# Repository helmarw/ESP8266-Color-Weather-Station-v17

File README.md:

#  Enhanced ESP8266 Color Weather Station w/ Touchscreen -- (Version v17, Open Weather Map) (based on original by Daniel Eichorn (squix78) modified for DHT22)

Original desctiption and instructions see here: https://github.com/fowlerk/ESP8266-Color-Weather-Station-v17

Changes:
 mod for DHTesp.h and DHT22, if you want to use DHT11 you have to change the line 
 dht.setup(DHTPIN, DHTesp::DHT22); and replace DHT22 by DHT11
 had to change some wiring, LED=D0, CS=D8 and DHT=D1, details see below
 added WiFiManager.h v01.14 zu src, since its the last one which is working with this code

## Wiring

| ILI9341   | NodeMCU | WeMos D1 Mini |  Comments | 
| --------- |:---------:|:---------------:|:---------------:|
| T_IRQ     | D4    | D4  |  |
| T_DO      | D6    | D6  |  |
| T_DIN     | D7    | D7  |  |
| T_CS      | D3    | D3  |  |
| T_CLK     | D5    | D5  |  |
| SDO/MISO  | D6    | D6  |  |
| LED       | D0    | D0  | since LED doesnt need interrupt, default was D8 |
| SCK       | D5    | D5  |  |
| SDI/MOSI  | D7    | D7  |  |
| DC/RS     | D2    | D2  |  |
| RESET     | RST   | RST |  |
| CS        | D8    | D8  | needed D1 for DHT, since DHT and D8 crashed ESP, default was D1 |
| GND       | GND   | GND |  |
| VCC       | 3V3   | 3V3 |  |
| DHTdata   | D1    | D1  |  |
| DHTV+     | 3V3   | 3V3 |  |
| DHTGND    | GND   | GND |  |

**Note that I have not tested the NodeMCU 

##  Contributed Libraries / Core / IDE (and links)

Library / Core Referenced | Version | Description | Link
------------------ | ------- | ----------- | ----
**Arduino IDE** | 1.8.10 | Arduino IDE | <https://www.arduino.cc/en/Main/Software>
**ESP8266 core** | 2.5.2 | ESP8266 board definitions | <https://arduino-esp8266.readthedocs.io/en/2.5.2/installing.html>
**<FS.h>** | 2.5.2 | Part of ESP8266 core, SPIFFS filesystem support | <https://arduino-esp8266.readthedocs.io/en/2.5.2/installing.html>
**<Adafruit_GFX.h>** | 1.3.4 | Adafruit's core graphics library | <https://github.com/adafruit/Adafruit-GFX-Library>
**<Adafruit_ILI9341.h>** | 1.2.0 | Adafruit's ILI9341 LCD hardware-specific library | <https://github.com/adafruit/Adafruit_ILI9341>
**<SPI.h>** | 2.5.2 | Part of ESP8266 core, used for DHT temperature readings if used | <https://arduino-esp8266.readthedocs.io/en/2.5.2/installing.html>
**<math.h>** | 1.6.23 | Part of Arduino core, advanced math functions used for calculating wind-chill/heat-index
**<XPT2046_Touchscreen.h>** | 1.2.0 | XPT2046 library for touch-screen controller by Paul Stoffregen | <https://github.com/PaulStoffregen/XPT2046_Touchscreen>
**<WiFiManager.h>** | 0.14.0 | WiFi Manager library by Tzapu | <https://github.com/tzapu/WiFiManager> added to source
**<ArduinoJson.h>** | 5.13.4 | JSON library by Bblanchon | <https://github.com/bblanchon/ArduinoJson>
**<JsonListener.h>** | 1.0.5 | JSON streaming parser by Squix78 | <https://github.com/squix78/json-streaming-parser>
**<OpenWeatherMapCurrent.h>** | 1.6.6 | ESP8266 Weather Station client library by Squix78 - current conditions | <https://github.com/squix78/esp8266-weather-station>
**<OpenWeatherMapForecast.h>** | 1.6.6 | ESP8266 Weather Station client library by Squix78 - 5-day forecast | <https://github.com/squix78/esp8266-weather-station>
**<Astronomy.h>** | 1.6.6 | ESP8266 Weather Station Astronomy client library by Squix78 - sunrise/set, moon illumination, age, phase calcuations | <https://github.com/squix78/esp8266-weather-station>
**<SunMoonCalc.h>** | 1.6.6 | ESP8266 Weather Station sun/moon calculations (not currently used - maybe for future moonrise/set calcs?) | <https://github.com/squix78/esp8266-weather-station>
**<WundergroundClient.h>** | | (*** No longer used ***) | <https://github.com/squix78/esp8266-weather-station>
**<simpleDSTadjust.h>**	| 1.2.0 | Simple daylight-savings time adjustment by Neptune | <https://github.com/neptune2/simpleDSTadjust>
**"TimeZone.h"** | 1.2.2 | Time zone conversion library by JChristensen | <https://github.com/JChristensen/Timezone>
**"DHTesp.h"** | 1.17.0 | Bernd Giesecke's DHT sensor library for ESP | <https://github.com/beegee-tokyo/DHTesp>
**<Adafruit_Sensor.h>** | 1.0.2 | Adafruit's Unified Sensor library | <https://github.com/adafruit/Adafruit_Sensor>

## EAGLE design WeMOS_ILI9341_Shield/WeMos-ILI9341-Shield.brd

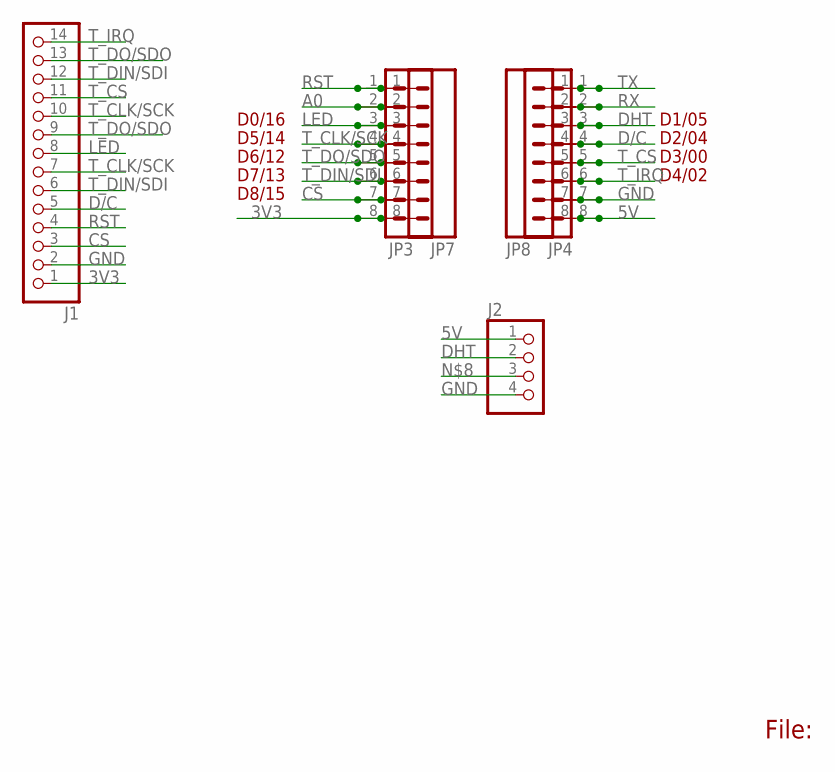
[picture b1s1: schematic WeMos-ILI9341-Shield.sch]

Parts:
J1: PINHD-1X14; 1X14
J2: HEADER-1X4; 1X04_OVAL
JP3, JP4, JP7, JP8: M08NO_SILK_FEMALE_PTH; 1X08_NO_SILK

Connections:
3V3: J1.1, JP3.8, JP7.8
5V: J2.1, JP4.8, JP8.8
A0: JP3.2, JP7.2
CS: J1.3, JP3.7, JP7.7
D/C: J1.5, JP4.4, JP8.4
DHT: J2.2, JP4.3, JP8.3
GND: J1.2, J2.4, JP4.7, JP8.7
LED: J1.8, JP3.3, JP7.3
RST: J1.4, JP3.1, JP7.1
RX: JP4.2, JP8.2
TX: JP4.1, JP8.1
T_CLK/SCK: J1.7, J1.10, JP3.4, JP7.4
T_CS: J1.11, JP4.5, JP8.5
T_DIN/SDI: J1.6, J1.12, JP3.6, JP7.6
T_DO/SDO: J1.9, J1.13, JP3.5, JP7.5
T_IRQ: J1.14, JP4.6, JP8.6

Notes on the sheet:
File:
D4/02
D3/00
D6/12
D2/04
D1/05
D7/13
D5/14
D8/15
D0/16

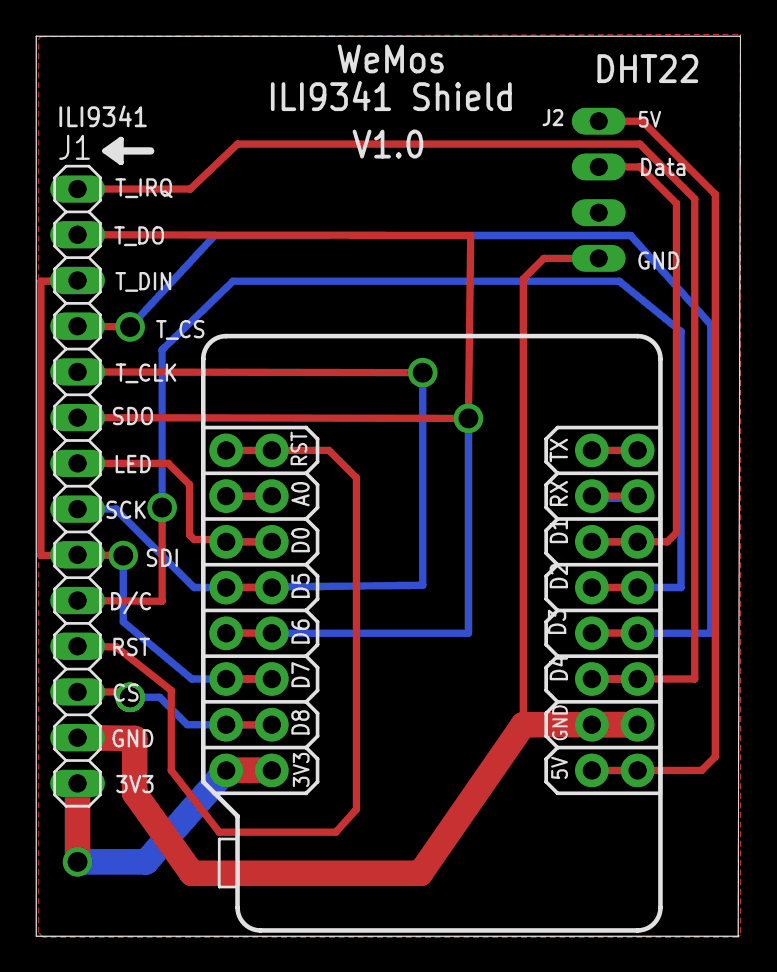
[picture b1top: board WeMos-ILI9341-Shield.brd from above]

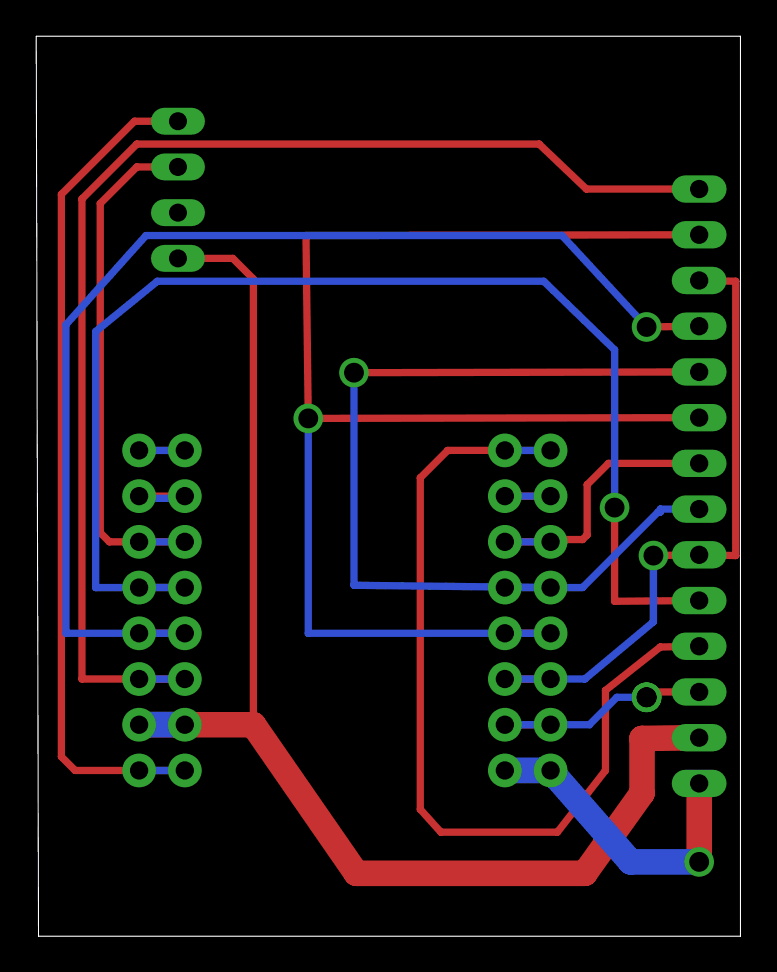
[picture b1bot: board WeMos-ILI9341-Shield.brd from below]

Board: 2 copper layers, 39.1 x 50.0 mm, 6 parts (4 on the bottom side), 16 nets.

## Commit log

2019-11-10 added support for DHT22 and local WifiManager.h
2019-11-10 initial version untested
2019-11-10 small bug fix
2019-11-10 small fix
2019-11-15 confirmed working shield
2019-11-15 sample images of working tft

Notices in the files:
parts and their libraries:
SparkFun-Connectors: Licensing: Creative Commons ShareAlike 4.0 International - https://creativecommons.org/licenses/by-sa/4.0
microbuilder: This work is placed in the public domain, and may be freely used for commercial and non-commercial work with the following conditions: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
